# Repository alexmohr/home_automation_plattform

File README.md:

# Home automation plattform 
PCB and schematic for my personal home automation plattform.
Contains temperature sensor, LDR, 433Mhz, 836Mhz, Infrared led, Infrared input. 
It provides an easy way to turn a raspberry pi into a home automation centre, when used together with home assistant. 

Made for raspberry pi 3 with ♥

## Used devices
[CC1101](https://www.aliexpress.com/item/CC1101-Wireless-Module-Long-Distance-Transmission-Antenna-868MHZ-M115/32635393463.html?spm=2114.search0104.3.8.588f8550vbZGhC&ws_ab_test=searchweb0_0,searchweb201602_5_10320_10152_10321_10065_10151_10344_10068_10342_10547_10343_10322_10340_10548_10341_10698_10697_10193_10696_10194_10084_10083_10618_10304_10307_10302_10180_10059_10184_308_100031_10319_10103_441_10624_10623_10622_10186_10621_10620,searchweb201603_15,ppcSwitch_5&algo_expid=a848840e-54c4-47bb-ab77-2ef09451083a-1&algo_pvid=a848840e-54c4-47bb-ab77-2ef09451083a&priceBeautifyAB=0)

[BME280](https://www.aliexpress.com/item/BME280-Digital-Sensor-Temperature-Humidity-Barometric-Pressure-Sensor-Module-I2C-SPI-1-8-5V-GY-BME280/32850070226.html?spm=2114.search0104.3.1.51d5301dEyf3TT&ws_ab_test=searchweb0_0,searchweb201602_5_10320_10152_10321_10065_10151_10344_10068_10342_10547_10343_10322_10340_10548_10341_10698_10697_10193_10696_10194_10084_10083_10618_10304_10307_10302_10180_10059_10184_308_100031_10319_10103_441_10624_10623_10622_10186_10621_10620,searchweb201603_15,ppcSwitch_5&algo_expid=3042d4b9-162d-4179-8373-1a698f202e66-0&algo_pvid=3042d4b9-162d-4179-8373-1a698f202e66&priceBeautifyAB=0)

[2TN2222A](https://www.aliexpress.com/item/2N2222A-Free-shipping-100pcs-in-line-triode-transistor-NPN-switching-transistors-TO-92-0-6A-30V/32816748799.html?spm=2114.search0104.3.15.5b0c6699WtyuTn&ws_ab_test=searchweb0_0,searchweb201602_5_10320_10152_10321_10065_10151_10344_10068_10342_10547_10343_10322_10340_10548_10341_10698_10697_10193_10696_10194_10084_10083_10618_10304_10307_10302_10180_10059_10184_308_100031_10319_10103_441_10624_10623_10622_10186_10621_10620,searchweb201603_15,ppcSwitch_5&algo_expid=e6ef298e-db4e-4916-be07-d07086949b34-2&algo_pvid=e6ef298e-db4e-4916-be07-d07086949b34&priceBeautifyAB=0)

[Infrared LED](https://www.aliexpress.com/item/10-Pcs-5mm-100mW-Infrared-IR-LED-Night-Vision-940nm-invisible-Diode-60-degree-Led-Light/32491780864.html?spm=2114.search0104.3.1.38356729QZHmb3&ws_ab_test=searchweb0_0,searchweb201602_5_10320_10152_10321_10065_10151_10344_10068_10342_10547_10343_10322_10340_10548_10341_10698_10697_10193_10696_10194_10084_10083_10618_10304_10307_10302_10180_10059_10184_308_100031_10319_10103_441_10624_10623_10622_10186_10621_10620,searchweb201603_15,ppcSwitch_5&algo_expid=32d9c39a-0b61-410d-89fb-16560a7c7f51-0&algo_pvid=32d9c39a-0b61-410d-89fb-16560a7c7f51&priceBeautifyAB=0)

[Generic 433Mhz Transmitter](https://www.aliexpress.com/item/433M-TX-RX-Super-regenerative-Module-Wireless-Transmitting-Module-Alarm-Transmitter-Receiver/2024422377.html?spm=2114.search0104.3.1.3fd544fbW57O9k&ws_ab_test=searchweb0_0,searchweb201602_5_10320_10152_10321_10065_10151_10344_10068_10342_10547_10343_10322_10340_10548_10341_10698_10697_10193_10696_10194_10084_10083_10618_10304_10307_10302_10180_10059_10184_308_100031_10319_10103_441_10624_10623_10622_10186_10621_10620,searchweb201603_15,ppcSwitch_5&algo_expid=0122146b-dcd8-4e24-963f-864d1bfaabf2-0&algo_pvid=0122146b-dcd8-4e24-963f-864d1bfaabf2&priceBeautifyAB=0)

Not linked: 
- 10k Ohm resistor
- 0.22 Farad Capacitor ( because basically it is redicously too large but was lying arround. Any other 5V capacitor will do just fine. The light threshold must be adjusted acordingly ) 

See https://github.com/alexmohr/raspberrypi-mqtt-light-sensor

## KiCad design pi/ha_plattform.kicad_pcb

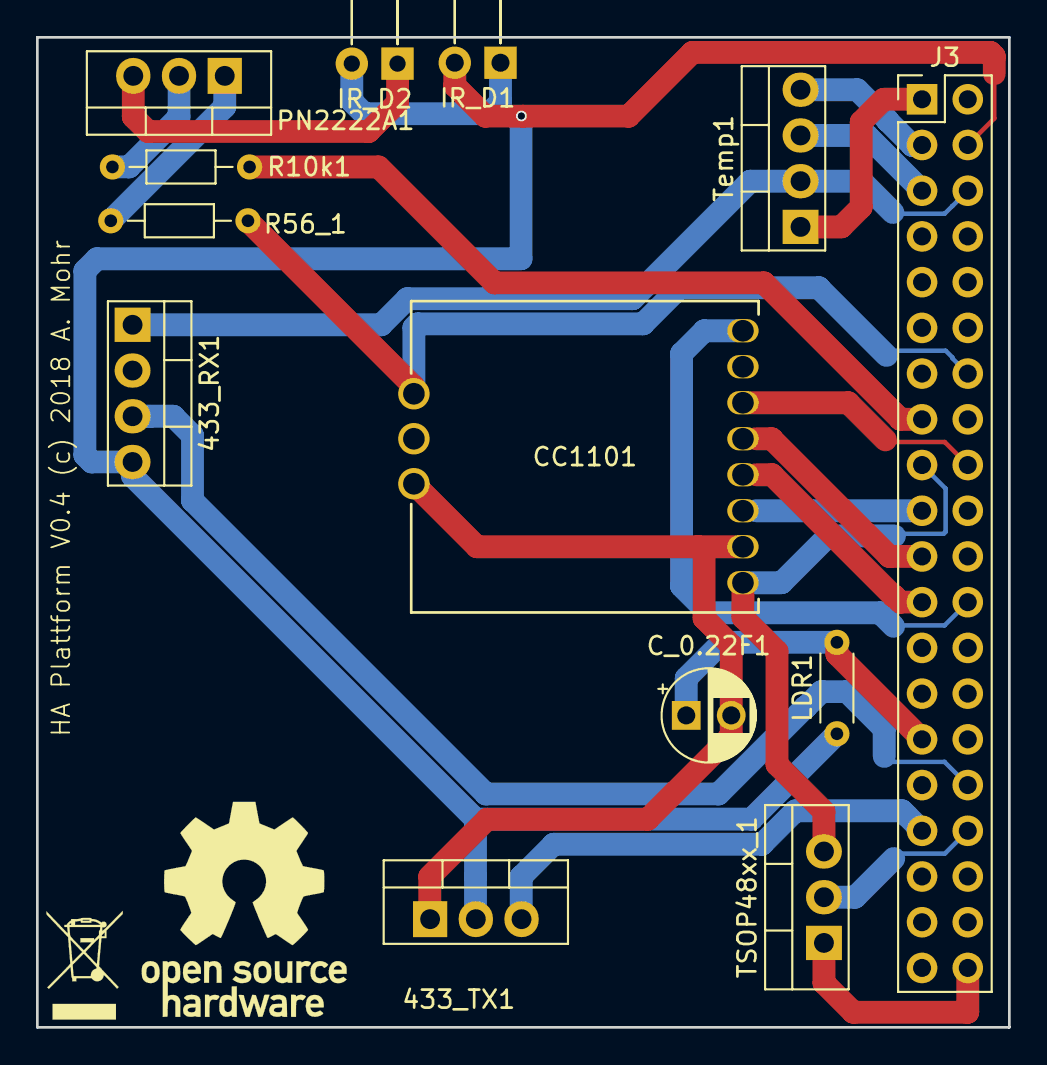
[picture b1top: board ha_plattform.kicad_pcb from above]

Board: 2 copper layers, 54.0 x 55.0 mm, 13 parts (0 on the bottom side), 22 nets.

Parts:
433_RX1: 433 Mhz receive; TO-220-4_Vertical
433_TX1: 433 MHz transmit; TO-220-3_Vertical
CC1101: CC1101-868MHz-Module
C_0.22F1: 0.22F; CP_Radial_D5.0mm_P2.50mm
IR_D1, IR_D2: IRL81A; LED_D3.0mm_Horizontal_O6.35mm_Z10.0mm
J3: Raspberry_Pi_2_3; PinHeader_2x20_P2.54mm_Vertical
LDR1: LDR03; R_Axial_DIN0204_L3.6mm_D1.6mm_P5.08mm_Horizontal
PN2222A1: PN2222A; TO-220-3_Vertical
R10k1: R10k; R_Axial_DIN0204_L3.6mm_D1.6mm_P7.62mm_Horizontal
R56_1: R; R_Axial_DIN0204_L3.6mm_D1.6mm_P7.62mm_Horizontal
TSOP48xx_1: TSOP45xx_0; TO-220-3_Vertical
Temp1: Temperature I2C; TO-220-4_Vertical

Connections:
unnamed: 433_RX1.1, J3.6, Temp1.2
unnamed: 433_RX1.3, J3.32
unnamed: 433_RX1.4, 433_TX1.2, IR_D1.2, J3.4, LDR1.1
unnamed: 433_TX1.1, CC1101.2, CC1101.9, CC1101.11, C_0.22F1.2, J3.14, R56_1.2
unnamed: 433_TX1.3, J3.33
unnamed: CC1101.1, J3.17, TSOP48xx_1.3
unnamed: CC1101.3, J3.19
unnamed: CC1101.4, J3.23
unnamed: CC1101.5, J3.21
unnamed: CC1101.6, J3.18
unnamed: CC1101.8, J3.24
unnamed: C_0.22F1.1, J3.29, LDR1.2
unnamed: IR_D1.1, IR_D2.2
unnamed: IR_D2.1, PN2222A1.3
unnamed: J3.1, Temp1.1
unnamed: J3.3, Temp1.4
unnamed: J3.5, Temp1.3
unnamed: J3.15, R10k1.1
unnamed: J3.34, TSOP48xx_1.2
unnamed: J3.40, TSOP48xx_1.1
unnamed: PN2222A1.1, R56_1.1
unnamed: PN2222A1.2, R10k1.2

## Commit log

2018-04-20 Inital commit
2018-04-22 I new file: _autosave-ha_plattform.kicad_pcb
2018-04-22 Added static images to view wihtout kicad
2018-04-23 Changed track width, improved routing
2018-04-23 changed details for fabrication
2018-05-15 Reduced layout size to fit into case
2018-05-15 Increased space between 433mhz modules
2018-05-17 fixed layout issues. moved led to front. rerouted whole board
2018-05-17 Updated images and gerber files. Added don't trash and open hardware symbol
2018-05-18 Changed minor things
2018-05-21 reduced footprint for capacitor
2018-05-24 Updated gerber files. Prepared for manufacturing
2018-06-07 Fixed layout, so the pinheader are on the correct side...
2018-06-08 Prepared version 0.3.
2018-06-24 Added layout for nodemcu
2018-06-29 Rerouted because footprints of 433mhz rx/tx were wrong-32-51.sch
2018-08-02 fixed size for node mcu

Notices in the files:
pi/ha_plattform.kicad_pcb:
HA Plattform V0.4 (c) 2018 A. Mohr
